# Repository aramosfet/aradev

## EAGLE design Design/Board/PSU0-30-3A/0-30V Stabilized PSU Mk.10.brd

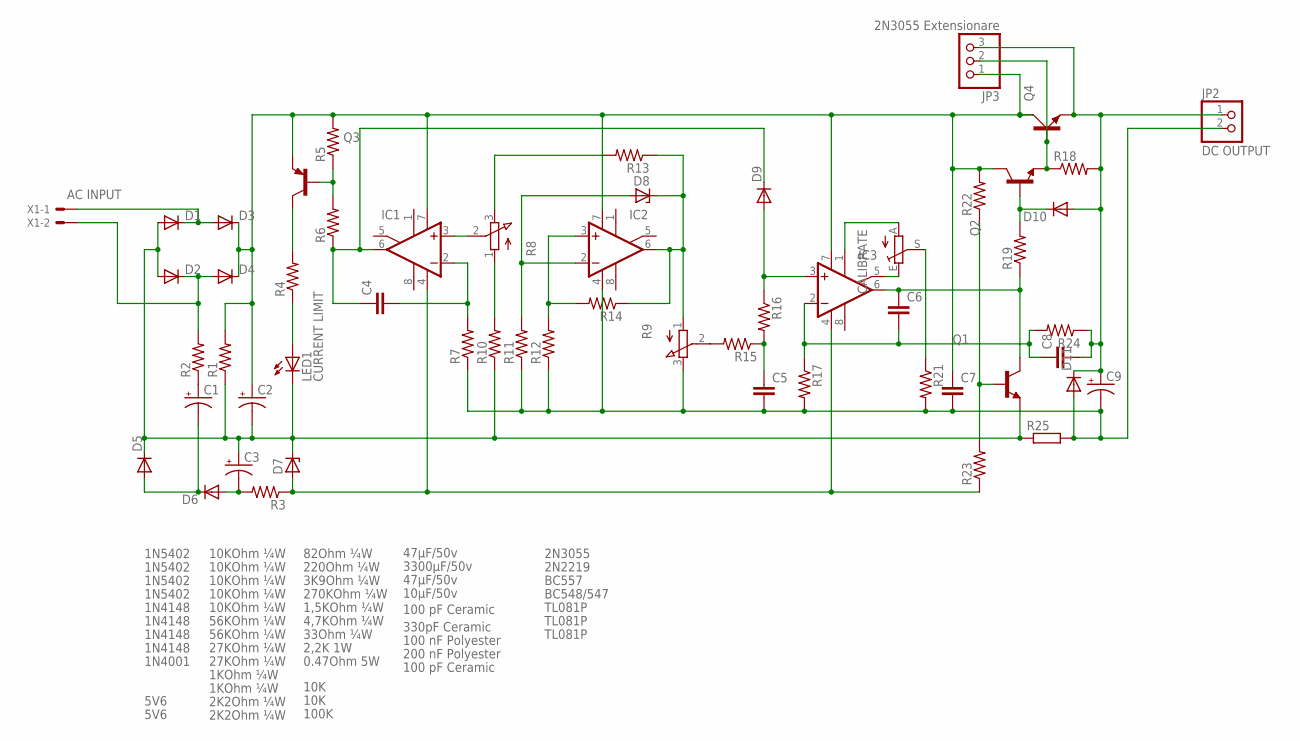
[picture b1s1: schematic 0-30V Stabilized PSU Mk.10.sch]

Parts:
C1, C3: 47µF/50v; TT2D4
C2: 3300µF/50v; EB20D
C4: 330pF Ceramic; C025-024X044
C5: 100 nF Polyester; C050-025X075
C6, C8: 100 pF Ceramic; C050-024X044
C7: 200 nF Polyester; C075-032X103
C9: 10µF/50v; E5-4
CALIBRATE: 100K; CA6V
D1, D2, D3, D4: 1N5402; DO201-15
D5, D6: 1N4148; DO35-10
D7, D8: 5V6; DO34Z7
D9, D10: 1N4148; DO35-7
D11: 1N4001; DO35-7
IC1, IC2, IC3: TL081P; DIL08
JP2: DC OUTPUT; 1X02
JP3: 2N3055 Extensionare; 1X03
LED1: CURRENT LIMIT; LED3MM
Q1: BC548/547; TO92-EBC
Q2: 2N2219; TO5
Q3: BC557; TO92-EBC
Q4: 2N3055; TO3A
R1: 2,2K 1W; P0613/15
R2: 82Ohm ¼W; 0204/7
R3: 220Ohm ¼W; 0204/7
R4: 3K9Ohm ¼W; 0204/7
R5, R16: 2K2Ohm ¼W; 0204/7
R6, R7, R12, R14, R22: 10KOhm ¼W; 0204/7
R8, R9: 10K; 3RP/1610N
R10: 33Ohm ¼W; 0204/7
R11: 4,7KOhm ¼W; 0204/7
R13, R24: 56KOhm ¼W; 0204/7
R15, R17: 27KOhm ¼W; 0204/7
R18, R19: 1KOhm ¼W; 0207/2V
R21: 270KOhm ¼W; 0204/7
R23: 1,5KOhm ¼W; 0204/7
R25: 0.47Ohm 5W; VTA54
X1: AC INPUT; 22-23-2021

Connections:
0-30VDC: C8.2, C9.+, D10.A, D11.C, JP2.1, JP3.3, Q4.E, R18.2, R24.1
0VAC: D1.C, D3.A, X1.1
24VAC: D2.C, D4.A, R2.2, X1.2
GND: C5.2, C7.2, C9.-, D11.A, IC2.4 (V-), JP2.2, R7.1, R9.3 (E), R11.1, R12.1, R17.2, R21.2, R25.2
unnamed: LED1.A, R4.1
unnamed: C1.-, D5.A, D6.C
unnamed: C1.+, R2.1
unnamed: Q3.C, R4.2
unnamed: Q3.B, R5.1, R6.2
unnamed: C3.-, D6.A, R3.2
unnamed: D7.A, IC1.4 (V-), IC3.4 (V-), R3.1, R23.1
unnamed: C4.1, D9.C, IC1.6 (OUT), R6.1
unnamed: C4.2, IC1.2 (-IN), R7.2
unnamed: IC1.3 (+IN), R8.2 (S)
unnamed: R8.1 (A), R10.2
unnamed: C2.-, C3.+, D1.A, D2.A, D5.C, D7.C, LED1.K (C), Q1.E, R1.1, R10.1, R25.1
unnamed: D8.C, IC2.6 (OUT), R9.1 (A), R13.1, R14.1
unnamed: IC2.3 (+IN), R12.2, R14.2
unnamed: D8.A, IC2.2 (-IN), R11.2
unnamed: R8.3 (E), R13.2
unnamed: R9.2 (S), R15.2
unnamed: C5.1, R15.1, R16.2
unnamed: D9.A, IC3.3 (+IN), R16.1
unnamed: JP3.2, Q2.1 (E), Q4.B, R18.1
unnamed: D10.C, Q2.2 (B), R19.2
unnamed: C6.1, IC3.6 (OUT), Q1.C, R19.1
unnamed: CALIBRATE.E, IC3.5 (ON2)
unnamed: CALIBRATE.A, IC3.1 (ON1)
unnamed: CALIBRATE.S, R21.1
unnamed: Q1.B, R22.1, R23.2
unnamed: C2.+, C7.1, D3.C, D4.C, IC1.7 (V+), IC2.7 (V+), IC3.7 (V+), JP3.1, Q2.3 (C), Q3.E, Q4.C, Q4.C1 (C), R1.2, R5.2, R22.2
unnamed: C6.2, C8.1, IC3.2 (-IN), R17.1, R24.2

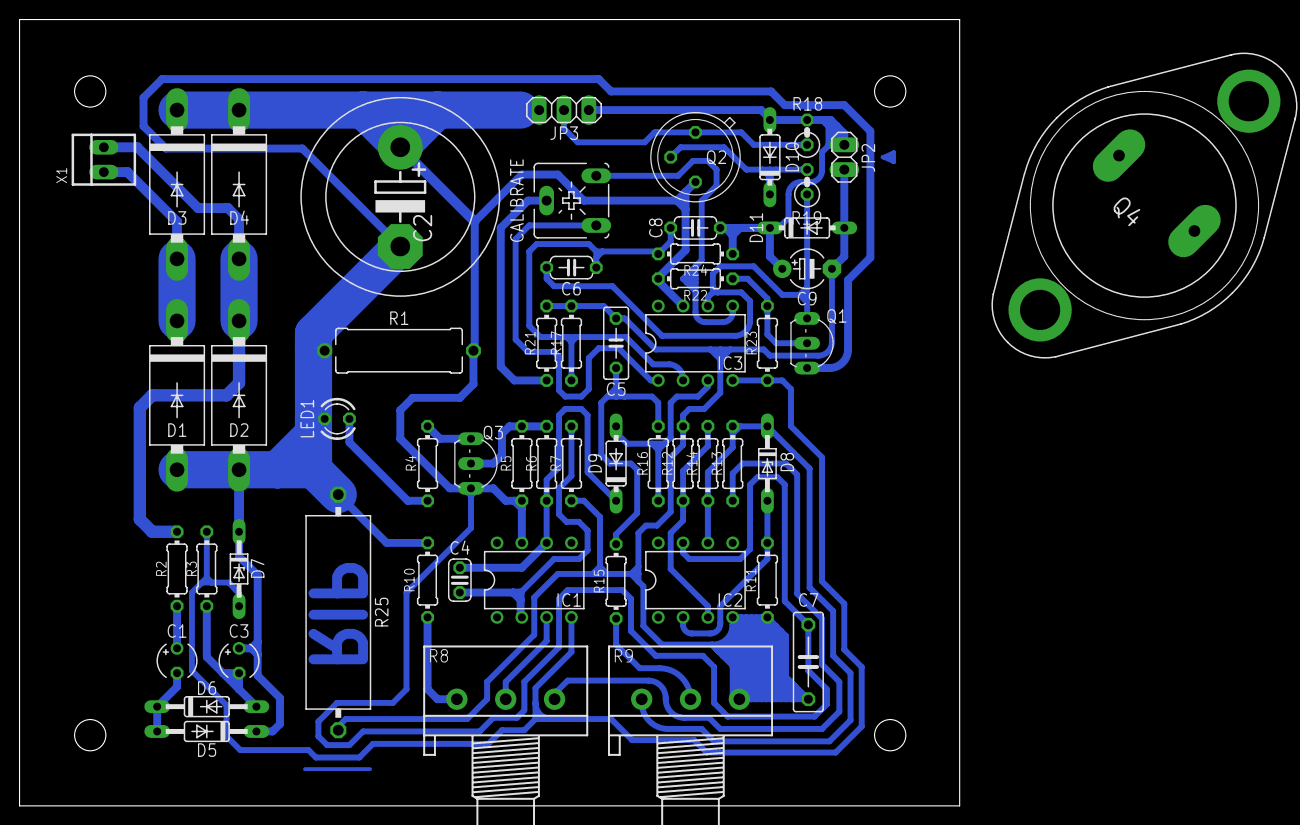
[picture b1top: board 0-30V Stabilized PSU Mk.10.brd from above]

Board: 2 copper layers, 96.3 x 80.5 mm, 56 parts (0 on the bottom side), 32 nets.

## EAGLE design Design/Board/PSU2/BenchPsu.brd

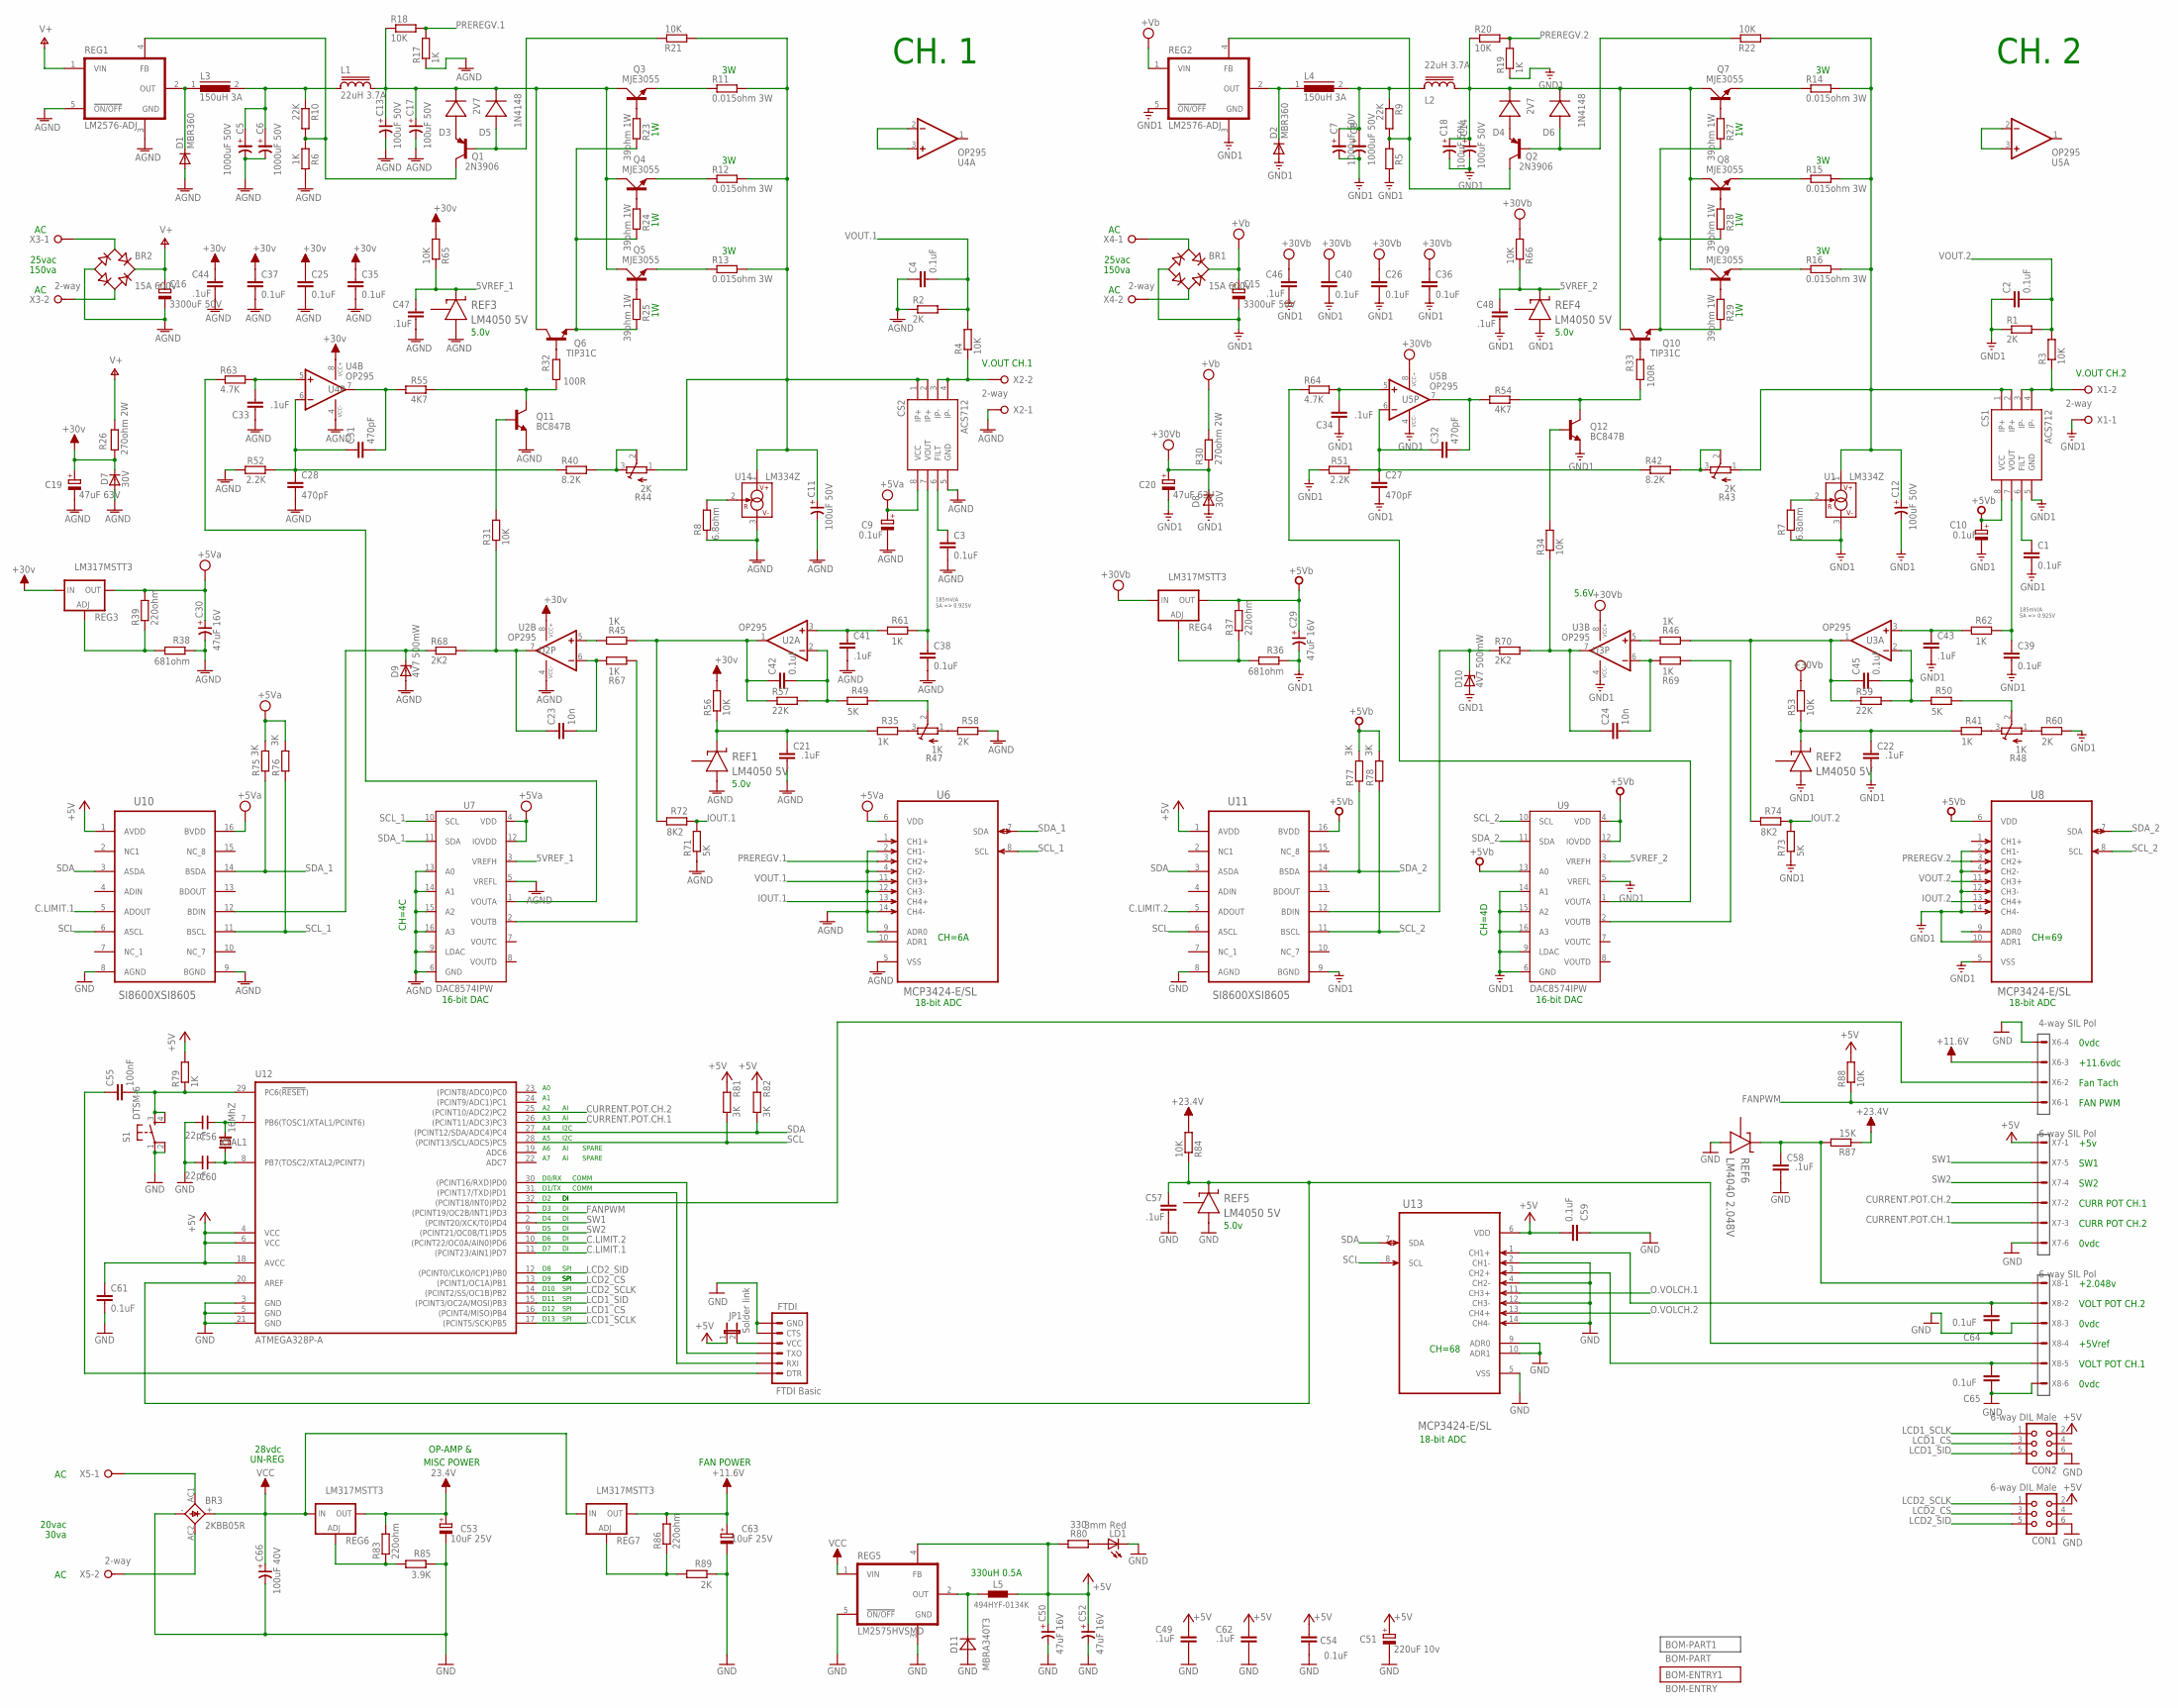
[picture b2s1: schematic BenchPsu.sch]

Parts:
BR1, BR2: 15A 600V; GSIB_15A
BR3: 2KBB05R; 2KBB-R; PARTNO RS 700-5330
C1, C2, C3, C4, C25, C26, C35, C36, C37, C38, C39, C40, C42, C45, C54, C59, C61, C64, C65: 0.1uF; C0805
C5, C6, C7, C8: 1000uF 50V; E5,0-12
C9, C10: 0.1uF; E2-5
C11, C12: 100uF 50V; E-050X125; PARTNO RS 365-4329
C13, C14, C17, C18: 100uF 50V; E-035X080; PARTNO RS 737-4421
C15, C16: 3300uF 50V; E7,5-18; PARTNO RS 684-2030
C19: 47uF 63V; E2,5-7; PARTNO IanJ Stock
C20: 47uF 63V; E2,5-7; PARTNO IanJ stock
C21, C22, C33, C34, C41, C43, C44, C46, C47, C48, C49, C57, C58, C62: .1uF; C0805
C23, C24: 10n; C0805
C27, C28, C31, C32: 470pF; C0805
C29, C50, C52: 47uF 16V; SV-C; PARTNO *
C30: 47uF 16V; SV-C
C51: 220uF 10v; E2-5
C53, C63: 10uF 25V; E2-5
C55: 100nF; C0805
C56, C60: 22pF; ENP-015-040; PARTNO Through hole
C66: 100uF 40V; SV-E/F
CON1, CON2: 6-way DIL Male; CON06
CS1, CS2: ACS712; SO08
D1, D2: MBR360; DO-201-15_V
D3, D4: 2V7; SOD123
D5, D6: 1N4148; SOD123
D7, D8: 30V; D015-12_V
D9, D10: 4V7 500mW; SOD80C
D11: MBRA340T3; SMA
FTDI: FTDI Basic; 1X06
JP1: Solder link; JP1
L1, L2: 22uH 3.7A; RS749-8366_THT22UH; PARTNO RS 749-8366
L3, L4: 150uH 3A; SFT1030; PARTNO RS 742-7991
L5: 494HYF-0134K; 0.2PIN_0.3DIA
LD1: 3mm Red; LED3MM
Q1, Q2: 2N3906; SOT23-BEC
Q3, Q4, Q5, Q7, Q8, Q9: MJE3055; TO220AV
Q6, Q10: TIP31C; TO220V
Q11, Q12: BC847B; SOT23
R1, R2, R58, R60, R89: 2K; R0805
R3, R4, R18, R20, R21, R22, R31, R34, R53, R56, R65, R66, R84, R88: 10K; R0805
R5, R6, R17, R19, R35, R41, R45, R46, R61, R62, R67, R69, R79: 1K; R0805
R7, R8: 6.8ohm; R0805
R9, R10, R57, R59: 22K; R0805
R11, R12, R13, R14, R15, R16: 0.015ohm 3W; R2512; PARTNO RS 720-3164
R23, R24, R25, R27, R28, R29: 39ohm 1W; 0411V
R26, R30: 270ohm 2W; P0613V
R32, R33: 100R; R0805
R36, R38: 681ohm; R0805
R37, R39, R83, R86: 220ohm; R0805
R40, R42: 8.2K; R0805
R43, R44: 2K; SM-42/43W
R47: 1K; 3223W
R48: 1K; SM-42/43W
R49, R50, R71, R73: 5K; R0805
R51, R52: 2.2K; R0805
R54, R55: 4K7; R0805
R63, R64: 4.7K; R0805
R68, R70: 2K2; R0805
R72, R74: 8K2; R0805
R75, R76, R77, R78, R81, R82: 3K; R0805
R80: 330; R0805
R85: 3.9K; R0805
R87: 15K; R0805
REF1, REF2: LM4050 5V; SOT95P237X112-3N
REF3, REF4, REF5: LM4050 5V; SOT95P237X112-3N; MPN LM4040A20IDBZT
REF6: LM4040 2.048V; SOT95P237X112-3N
REG1, REG2: LM2576-ADJ; LM2575HV_V_2
REG3, REG4, REG6, REG7: LM317MSTT3; SOT223
REG5: LM2575HVSMD; TO263-5
S1: DTSM-6
U1, U14: LM334Z; TO92
U2, U3, U4, U5: OP295; SO08
U6, U8, U13: MCP3424-E/SL; SOIC127P600X175-14N
U7, U9: DAC8574IPW; TSSOP16
U10, U11: SI8600XSI8605; SOIC16N
U12: ATMEGA328P-A; TQFP32A
X1, X2, X3, X4, X5: 2-way; W237-132
X6: 4-way SIL Pol; 22-23-2041
X7, X8: 6-way SIL Pol; 22-23-2061
XTAL1: 16MhZ; HC49/S@1

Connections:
2.048V: C58.1, R87.2, REF6.1 (CATHODE), X8.1
5VREF_1: C47.1, R65.1, REF3.1 (CATHODE), U7.3 (VREFH)
5VREF_2: C48.1, R66.1, REF4.1 (CATHODE), U9.3 (VREFH)
+5V: C49.1, C50.+, C51.+, C52.+, C54.2, C59.1, C61.1, C62.1, CON1.2, CON2.2, JP1.1, L5.2, R79.2, R80.1, R81.2, R82.2, R88.2, REG5.4 (FB), U10.1 (AVDD), U11.1 (AVDD), U12.4 (VCC), U12.6 (VCC), U12.18 (AVCC), U13.6 (VDD), X7.1
+5VT: C10.+, C29.+, CS1.8 (VCC), R37.2, R77.2, R78.2, REG4.4 (OUT), U8.6 (VDD), U9.4 (VDD), U9.12 (IOVDD), U9.13 (A0), U11.16 (BVDD)
+12V: C63.+, R86.2, REG7.4 (OUT), X6.3
+24V: C53.+, R83.2, R84.2, R87.1, REG6.4 (OUT)
AGND: BR2.-, C3.2, C4.1, C5.-, C6.-, C9.-, C11.-, C13.-, C16.-, C17.-, C19.-, C21.2, C25.2, C28.2, C30.-, C33.1, C35.2, C37.2, C38.2, C41.2, C44.2, C47.2, CS2.5 (GND), D1.A, D7.A, D9.A, Q11.2 (E), R2.1, R6.2, R8.1, R17.1, R38.1, R52.1, R58.2, R71.1, REF1.2 (A), REF3.2 (A), REG1.3 (GND), REG1.5 (!ON/OFF), U2.4 (VCC-), U4.4 (VCC-), U6.2 (CH1-), U6.4 (CH2-), U6.5 (VSS), U6.9 (ADR0), U6.12 (CH3-), U6.14 (CH4-), U7.5 (VREFL), U7.6 (GND), U7.9 (LDAC), U7.13 (A0), U7.14 (A1), U7.15 (A2), U7.16 (A3), U10.9 (BGND), U14.3 (V-), X2.1
AVCC: C19.+, C25.1, C35.1, C37.1, C44.1, D7.C, R26.1, R56.2, R65.2, REG3.3 (IN), U2.8 (VCC+), U4.8 (VCC+)
C.LIMIT.1: U10.5 (ADOUT), U12.11 ((PCINT23/AIN1)PD7)
C.LIMIT.2: U11.5 (ADOUT), U12.10 ((PCINT22/OC0A/AIN0)PD6)
CURRENT.POT.CH.1: U12.26 ((PCINT11/ADC3)PC3), X7.3
CURRENT.POT.CH.2: U12.25 ((PCINT10/ADC2)PC2), X7.2
FANPWM: R88.1, U12.1 ((PCINT19/OC2B/INT1)PD3), X6.1
GND: BR3.-, C49.2, C50.-, C51.-, C52.-, C53.-, C54.1, C56.1, C57.2, C58.2, C59.2, C60.1, C61.2, C62.2, C63.-, C64.2, C65.2, C66.-, CON1.6, CON2.6, D11.A, FTDI.5 (CTS), FTDI.6 (GND), LD1.K (C), R85.1, R89.1, REF5.2 (A), REF6.2 (A), REG5.3 (GND), REG5.5 (!ON/OFF), S1.1, S1.2, U10.8 (AGND), U11.8 (AGND), U12.3 (GND), U12.5 (GND), U12.21 (GND), U13.2 (CH1-), U13.4 (CH2-), U13.5 (VSS), U13.9 (ADR0), U13.10 (ADR1), U13.12 (CH3-), U13.14 (CH4-), X6.4, X7.6, X8.3, X8.6
GND1: BR1.-, C1.2, C2.1, C7.-, C8.-, C10.-, C12.-, C14.-, C15.-, C18.-, C20.-, C22.2, C26.2, C27.2, C29.-, C34.1, C36.2, C39.2, C40.2, C43.2, C46.2, C48.2, CS1.5 (GND), D2.A, D8.A, D10.A, Q12.2 (E), R1.1, R5.2, R7.1, R19.1, R36.1, R51.1, R60.2, R73.1, REF2.2 (A), REF4.2 (A), REG2.3 (GND), REG2.5 (!ON/OFF), U1.3 (V-), U3.4 (VCC-), U5.4 (VCC-), U8.2 (CH1-), U8.4 (CH2-), U8.5 (VSS), U8.10 (ADR1), U8.12 (CH3-), U8.14 (CH4-), U9.5 (VREFL), U9.6 (GND), U9.9 (LDAC), U9.14 (A1), U9.15 (A2), U9.16 (A3), U11.9 (BGND), X1.1
IOUT.1: R71.2, R72.2, U6.13 (CH4+)
IOUT.2: R73.2, R74.2, U8.13 (CH4+)
LCD1_CS: CON2.3, U12.16 ((PCINT4/MISO)PB4)
LCD1_SCLK: CON2.1, U12.17 ((PCINT5/SCK)PB5)
LCD1_SID: CON2.5, U12.15 ((PCINT3/OC2A/MOSI)PB3)
LCD2_CS: CON1.3, U12.13 ((PCINT1/OC1A)PB1)
LCD2_SCLK: CON1.1, U12.14 ((PCINT2/SS/OC1B)PB2)
LCD2_SID: CON1.5, U12.12 ((PCINT0/CLKO/ICP1)PB0)
unnamed: R38.2, R39.1, REG3.1 (ADJ)
unnamed: BR3.AC1, X5.1
unnamed: D11.C, L5.1, REG5.2 (OUT)
unnamed: BR3.AC2, X5.2
unnamed: R47.2 (S), R49.2
unnamed: C42.2, R49.1, R57.2, U2.2 (-IN)
unnamed: C5.+, C6.+, L1.1, L3.2, R10.1
unnamed: C41.1, R61.1, U2.3 (+IN)
unnamed: Q1.C, R6.1, R10.2, REG1.4 (FB)
unnamed: D3.A (+), Q1.E
unnamed: D5.A (+), Q1.B, R21.2
unnamed: R83.1, R85.2, REG6.1 (ADJ)
unnamed: C31.2, R55.1, U4.7 (OUT)
unnamed: C28.1, C31.1, R40.1, R52.2, U4.6 (-IN)
unnamed: Q11.1 (B), R31.2
unnamed: C23.1, R31.1, R68.2, U2.7 (OUT)
unnamed: R40.2, R44.2 (S), R44.3 (E)
unnamed: R64.1, U9.1 (VOUTA)
unnamed: BR2.AC1, X3.1
unnamed: U12.32 ((PCINT18/INT0)PD2), X6.2
unnamed: LD1.A, R80.2
unnamed: C57.1, R84.1, REF5.1 (CATHODE), U12.20 (AREF), X8.4
unnamed: C38.1, CS2.7 (VOUT), R61.2
unnamed: Q3.B, R23.1
unnamed: C55.1, FTDI.1 (DTR)
unnamed: C33.2, R63.2, U4.5 (+IN)
unnamed: R35.2, R47.3 (E)
unnamed: Q4.B, R24.1
unnamed: R69.2, U9.2 (VOUTB)
unnamed: U4.2 (-IN), U4.3 (+IN)
unnamed: D10.C, R70.1, U11.12 (BDIN)
unnamed: R47.1 (A), R58.1
unnamed: FTDI.4 (VCC), JP1.2
unnamed: R63.1, U7.1 (VOUTA)
unnamed: Q11.3 (C), R32.2, R55.2
unnamed: C56.2, U12.7 (PB6(TOSC1/XTAL1/PCINT6)), XTAL1.2
unnamed: C60.2, U12.8 (PB7(TOSC2/XTAL2/PCINT7)), XTAL1.1
unnamed: U5.2 (-IN), U5.3 (+IN)
unnamed: C55.2, R79.1, S1.3, S1.4, U12.29 (PC6(!RESET!))
unnamed: R36.2, R37.1, REG4.1 (ADJ)
unnamed: R41.2, R48.3 (E)
unnamed: R48.1 (A), R60.1
unnamed: R8.2, U14.2 (R)
unnamed: C22.1, R41.1, R53.1, REF2.1 (CATHODE)
unnamed: D9.C, R68.1, U10.12 (BDIN)
unnamed: Q5.B, R25.1
unnamed: C3.1, CS2.6 (FILT)
unnamed: C65.1, U13.3 (CH2+), X8.5
unnamed: C45.2, R50.1, R59.2, U3.2 (-IN)
unnamed: C43.1, R62.1, U3.3 (+IN)
unnamed: R86.1, R89.2, REG7.1 (ADJ)
unnamed: FTDI.2 (RXI), U12.31 ((PCINT17/TXD)PD1)
unnamed: R45.1, U2.5 (+IN)
unnamed: FTDI.3 (TXO), U12.30 ((PCINT16/RXD)PD0)
unnamed: C23.2, R67.1, U2.6 (-IN)
unnamed: D2.C, L4.1, REG2.2 (OUT)
unnamed: C27.1, C32.1, R42.1, R51.2, U5.6 (-IN)
unnamed: Q12.1 (B), R34.2
unnamed: C24.1, R34.1, R70.2, U3.7 (OUT)
unnamed: C39.1, CS1.7 (VOUT), R62.2
unnamed: R7.2, U1.2 (R)
unnamed: C7.+, C8.+, L2.1, L4.2, R9.1
unnamed: C34.2, R64.2, U5.5 (+IN)
unnamed: CS1.3 (IP-), CS1.4 (IP-), R3.1, X1.2
unnamed: C1.1, CS1.6 (FILT)
unnamed: C32.2, R54.1, U5.7 (OUT)
unnamed: D4.A (+), Q2.E
unnamed: Q12.3 (C), R33.2, R54.2
unnamed: D6.A (+), Q2.B, R22.2
unnamed: R48.2 (S), R50.2
unnamed: C24.2, R69.1, U3.6 (-IN)
unnamed: R46.1, U3.5 (+IN)
unnamed: R42.2, R43.2 (S), R43.3 (E)
unnamed: Q10.3 (E), R27.2, R28.2, R29.2
unnamed: C64.1, U13.1 (CH1+), X8.2
unnamed: BR1.AC2, X4.2
unnamed: Q6.3 (E), R23.2, R24.2, R25.2
unnamed: Q8.E, R15.1
unnamed: C21.1, R35.1, R56.1, REF1.1 (CATHODE)
unnamed: BR1.AC1, X4.1
unnamed: R67.2, U7.2 (VOUTB)
unnamed: CS2.3 (IP-), CS2.4 (IP-), R4.1, X2.2
unnamed: Q9.B, R29.1
unnamed: C11.+, CS2.1 (IP+), CS2.2 (IP+), R11.2, R12.2, R13.2, R21.1, R44.1 (A), U14.1 (V+)
unnamed: Q5.E, R13.1
unnamed: Q6.1 (B), R32.1
unnamed: Q9.E, R16.1
unnamed: Q7.B, R27.1
unnamed: Q8.B, R28.1
unnamed: Q10.1 (B), R33.1
unnamed: D1.C, L3.1, REG1.2 (OUT)
unnamed: Q3.E, R11.1
unnamed: Q4.E, R12.1
unnamed: BR2.AC2, X3.2
unnamed: Q7.E, R14.1
unnamed: C14.+, C18.+, D4.C (-), D6.C (-), L2.2, Q7.C, Q8.C, Q9.C, Q10.2 (C), R20.1
unnamed: Q2.C, R5.1, R9.2, REG2.4 (FB)
unnamed: C12.+, CS1.1 (IP+), CS1.2 (IP+), R14.2, R15.2, R16.2, R22.1, R43.1 (A), U1.1 (V+)
O.VOLCH.1: U13.11 (CH3+)
O.VOLCH.2: U13.13 (CH4+)
PREREGV.1: R17.2, R18.2, U6.3 (CH2+)
PREREGV.2: R19.2, R20.2, U8.3 (CH2+)
PREVOUT.1: C13.+, C17.+, D3.C (-), D5.C (-), L1.2, Q3.C, Q4.C, Q5.C, Q6.2 (C), R18.1
QQQ: C42.1, R45.2, R57.1, R72.1, U2.1 (OUT)
QQQ1: C45.1, R46.2, R59.1, R74.1, U3.1 (OUT)
SCL: R81.1, U10.6 (ASCL), U11.6 (ASCL), U12.28 ((PCINT13/SCL/ADC5)PC5), U13.8 (SCL)
SCL_1: R76.1, U6.8 (SCL), U7.10 (SCL), U10.11 (BSCL)
SCL_2: R78.1, U8.8 (SCL), U9.10 (SCL), U11.11 (BSCL)
SDA: R82.1, U10.3 (ASDA), U11.3 (ASDA), U12.27 ((PCINT12/SDA/ADC4)PC4), U13.7 (SDA)
SDA_1: R75.1, U6.7 (SDA), U7.11 (SDA), U10.14 (BSDA)
SDA_2: R77.1, U8.7 (SDA), U9.11 (SDA), U11.14 (BSDA)
SW1: U12.2 ((PCINT20/XCK/T0)PD4), X7.5
SW2: U12.9 ((PCINT21/OC0B/T1)PD5), X7.4
V+: BR2.+, C16.+, R26.2, REG1.1 (VIN)
VCC: BR3.+, C66.+, REG5.1 (VIN), REG6.3 (IN), REG7.3 (IN)
VDD: C20.+, C26.1, C36.1, C40.1, C46.1, D8.C, R30.1, R53.2, R66.2, REG4.3 (IN), U3.8 (VCC+), U5.8 (VCC+)
VEE: BR1.+, C15.+, R30.2, REG2.1 (VIN)
VOUT.1: C4.2, R2.2, R4.2, U6.11 (CH3+)
VOUT.2: C2.2, R1.2, R3.2, U8.11 (CH3+)
VPP: C9.+, C30.+, CS2.8 (VCC), R39.2, R75.2, R76.2, REG3.4 (OUT), U6.6 (VDD), U7.4 (VDD), U7.12 (IOVDD), U10.16 (BVDD)

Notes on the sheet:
330uH 0.5A
V.OUT CH.1
185mV/A 5A => 0.925V
D0/RX
D1/TX
D10
D11
D12
D13
I2C
SPI
COMM
SW2
SW1
0vdc
VOLT POT CH.2
VOLT POT CH.1
+2.048v
+5v
V.OUT CH.2
5.6V
20vac
UN-REG
25vac
150va
30va
CURR POT CH.2
CURR POT CH.1
28vdc
CH. 1
+11.6vdc
Fan Tach
FAN PWM
FAN POWER
16-bit DAC
18-bit ADC
5.0v
+5Vref
MISC POWER
OP-AMP &

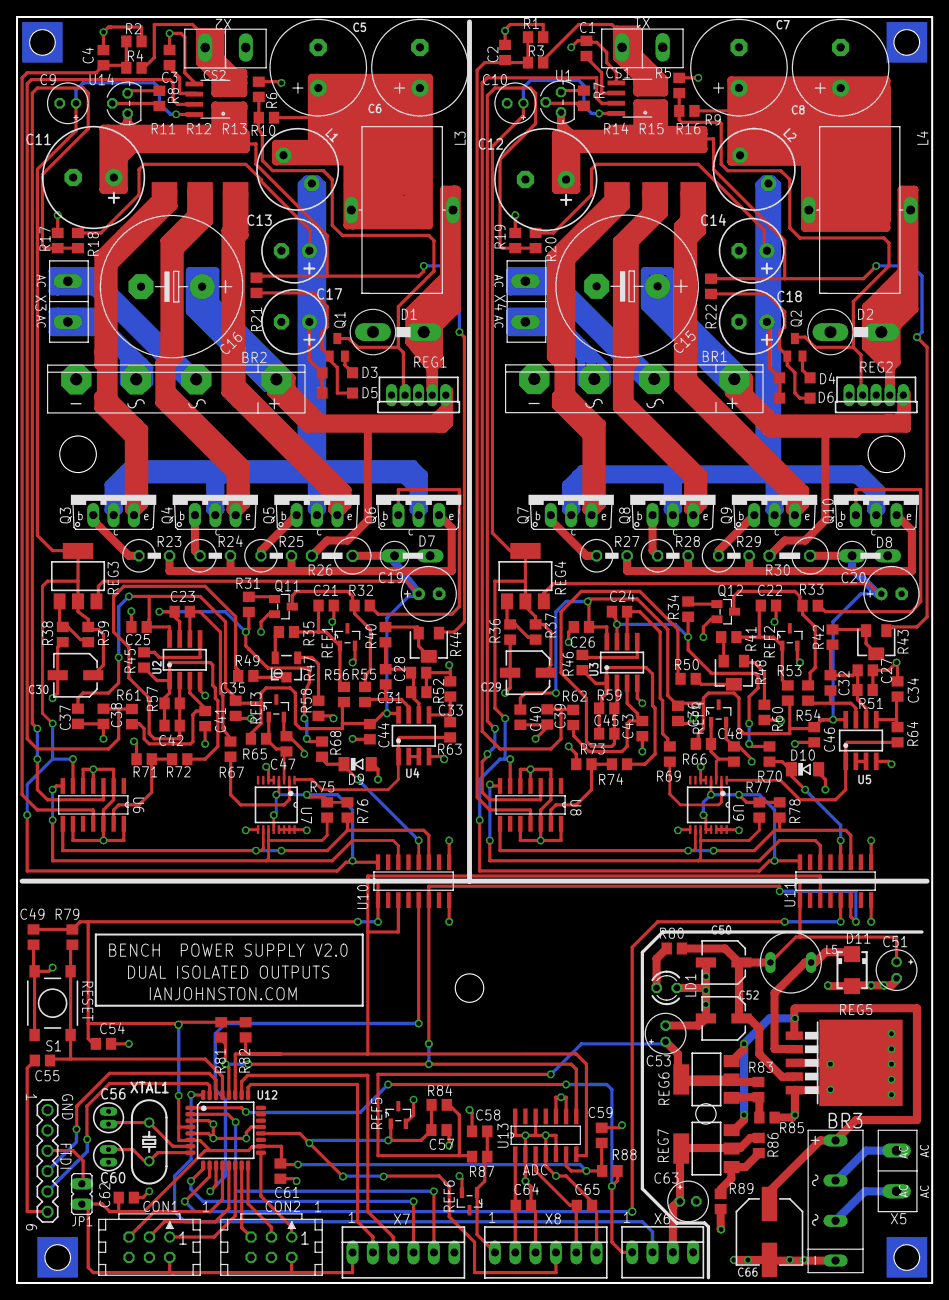
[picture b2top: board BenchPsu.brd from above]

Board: 2 copper layers, 114.3 x 158.1 mm, 230 parts (0 on the bottom side), 142 nets.

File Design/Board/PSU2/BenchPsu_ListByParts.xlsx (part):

Part | Value | Attributes | Package | Description | Part Num
BOM-ENTRY1 | BOM-ENTRY |  | * | BOM ENTRY | *
BOM-PART1 | BOM-PART |  | * | BOM ENTRY | *
BR1 | 15A 600V |  | GSIB_15A |  | *
BR2 | 15A 600V |  | GSIB_15A |  | *
BR3 | 2KBB05R |  | 2KBB-R | RECTIFIER | RS 700-5330
C1 | 0.1uF |  | C0805 | CAPACITOR, European symbol | *
C2 | 0.1uF |  | C0805 | CAPACITOR, European symbol | *
C3 | 0.1uF |  | C0805 | CAPACITOR, European symbol | *
C4 | 0.1uF |  | C0805 | CAPACITOR, European symbol | *
C5 | 1000uF 50V |  | E5,0-12 | POLARIZED RADIAL ELECTROLYTIC | *
C6 | 1000uF 50V |  | E5,0-12 | POLARIZED RADIAL ELECTROLYTIC | *
C7 | 1000uF 50V |  | E5,0-12 | POLARIZED RADIAL ELECTROLYTIC | *
C8 | 1000uF 50V |  | E5,0-12 | POLARIZED RADIAL ELECTROLYTIC | *
C9 | 0.1uF |  | E2-5 | POLARIZED CAPACITOR, European symbol | *
C10 | 0.1uF |  | E2-5 | POLARIZED CAPACITOR, European symbol | *
C11 | 100uF 50V |  | E-050X125 | POLARIZED CAP
C12 | 100uF 50V |  | E-050X125 | POLARIZED CAP
C13 | 100uF 50V |  | E-035X080 | POLARIZED CAP | RS 737-4421
C14 | 100uF 50V |  | E-035X080 | POLARIZED CAP | RS 737-4421
C15 | 3300uF 50V |  | E7,5-18 | POLARIZED CAPACITOR, European symbol | RS 684-2030
C16 | 3300uF 50V |  | E7,5-18 | POLARIZED CAPACITOR, European symbol | RS 684-2030
C17 | 100uF 50V |  | E-035X080 | POLARIZED CAP | RS 737-4421
C18 | 100uF 50V |  | E-035X080 | POLARIZED CAP | RS 737-4421
C19 | 47uF 63V |  | E2,5-7 | POLARIZED CAPACITOR, European symbol | IANJ STOCK
C20 | 47uF 63V |  | E2,5-7 | POLARIZED CAPACITOR, European symbol | IANJ STOCK
C21 | .1uF |  | C0805 | CAPACITOR, European symbol | *
C22 | .1uF |  | C0805 | CAPACITOR, European symbol | *
C23 | 10n |  | C0805 | CAPACITOR, European symbol | *
C24 | 10n |  | C0805 | CAPACITOR, European symbol | *
C25 | 0.1uF |  | C0805 | CAPACITOR, European symbol | *
C26 | 0.1uF |  | C0805 | CAPACITOR, European symbol | *
C27 | 470pF |  | C0805 | CAPACITOR, European symbol | *
C28 | 470pF |  | C0805 | CAPACITOR, European symbol | *
C29 | 47uF 16V |  | SV-C | POLARIZED CAP | *
C30 | 47uF 16V |  | SV-C | POLARIZED CAP | *
C31 | 470pF |  | C0805 | CAPACITOR, European symbol | *
C32 | 470pF |  | C0805 | CAPACITOR, European symbol | *
C33 | .1uF |  | C0805 | CAPACITOR, European symbol | *
C34 | .1uF |  | C0805 | CAPACITOR, European symbol | *
C35 | 0.1uF |  | C0805 | CAPACITOR, European symbol | *
C36 | 0.1uF |  | C0805 | CAPACITOR, European symbol | *
C37 | 0.1uF |  | C0805 | CAPACITOR, European symbol | *
C38 | 0.1uF |  | C0805 | CAPACITOR, European symbol | *
C39 | 0.1uF |  | C0805 | CAPACITOR, European symbol | *
C40 | 0.1uF |  | C0805 | CAPACITOR, European symbol | *
C41 | .1uF |  | C0805 | CAPACITOR, European symbol | *
C42 | 0.1uF |  | C0805 | CAPACITOR, European symbol | *
C43 | .1uF |  | C0805 | CAPACITOR, European symbol | *
C44 | .1uF |  | C0805 | CAPACITOR, European symbol | *
C45 | 0.1uF |  | C0805 | CAPACITOR, European symbol | *
C46 | .1uF |  | C0805 | CAPACITOR, European symbol | *
C47 | .1uF |  | C0805 | CAPACITOR, European symbol | *
C48 | .1uF |  | C0805 | CAPACITOR, European symbol | *
C49 | .1uF |  | C0805 | CAPACITOR, European symbol | *
C50 | 47uF 16V |  | SV-C | POLARIZED CAP | *
C51 | 220uF 10v |  | E2-5 | POLARIZED CAPACITOR, European symbol | *
C52 | 47uF 16V |  | SV-C | POLARIZED CAP | *
C53 | 10uF 25V |  | E2-5 | POLARIZED CAPACITOR, European symbol | *
C54 | 0.1uF |  | C0805 | CAPACITOR, European symbol | *
C55 | 100nF |  | C0805 | CAPACITOR, European symbol | *
C56 | 22pF |  | ENP-015-040 | BIPOLAR CAP | THROUGH HOLE
C57 | .1uF |  | C0805 | CAPACITOR, European symbol | *
C58 | .1uF |  | C0805 | CAPACITOR, European symbol | *
C59 | 0.1uF |  | C0805 | CAPACITOR, European symbol | *
C60 | 22pF |  | ENP-015-040 | BIPOLAR CAP | THROUGH HOLE
C61 | 0.1uF |  | C0805 | CAPACITOR, European symbol | *
C62 | .1uF |  | C0805 | CAPACITOR, European symbol | *
C63 | 10uF 25V |  | E2-5 | POLARIZED CAPACITOR, European symbol | *
C64 | 0.1uF |  | C0805 | CAPACITOR, European symbol | *
C65 | 0.1uF |  | C0805 | CAPACITOR, European symbol | *
C66 | 100uF 40V |  | SV-E/F | POLARIZED CAP | *
CON1 | 6-way DIL Male |  | CON06 | CONNECTOR | *
CON2 | 6-way DIL Male |  | CON06 | CONNECTOR | *
CS1 | ACS712 |  | SO08 |  | *
CS2 | ACS712 |  | SO08 |  | *
D1 | MBR360 |  | DO-201-15_V | DIODE | *
D2 | MBR360 |  | DO-201-15_V | DIODE | *
D3 | 2V7 |  | SOD123 |  | *
D4 | 2V7 |  | SOD123 |  | *
D5 | 1N4148 |  | SOD123 |  | *
D6 | 1N4148 |  | SOD123 |  | *
D7 | 30V |  | D015-12_V | DIODE | *
D8 | 30V |  | D015-12_V | DIODE | *
D9 | 4V7 500mW |  | SOD80C | Z-Diode | *
D10 | 4V7 500mW |  | SOD80C | Z-Diode | *
D11 | MBRA340T3 |  | SMA | Surface Mount Schottky Power Rectifier | *
FTDI | FTDI Basic |  | 1X06 |  | *
JP1 | Solder link |  | JP1 | JUMPER | *
L1 | 22uH 3.7A |  | RS749-8366_THT22UH | INDUCTOR | RS 749-8366
L2 | 22uH 3.7A |  | RS749-8366_THT22UH | INDUCTOR | RS 749-8366
L3 | 150uH 3A |  | SFT1030 | INDUCTOR | RS 742-7991
L4 | 150uH 3A |  | SFT1030 | INDUCTOR | RS 742-7991
L5 | 494HYF-0134K |  | 0.2PIN_0.3DIA | 330uH 0.54A | *
LD1 | 3mm Red |  | LED3MM | LED | *
Q1 | 2N3906 |  | SOT23-BEC | PNP Transistror | *
Q2 | 2N3906 |  | SOT23-BEC | PNP Transistror | *
Q3 | MJE3055 |  | TO220AV | NPN TRANSISTOR | *
Q4 | MJE3055 |  | TO220AV | NPN TRANSISTOR | *
Q5 | MJE3055 |  | TO220AV | NPN TRANSISTOR | *
Q6 | TIP31C |  | TO220V | NPN Transistor | *
Q7 | MJE3055 |  | TO220AV | NPN TRANSISTOR | *
Q8 | MJE3055 |  | TO220AV | NPN TRANSISTOR | *
Q9 | MJE3055 |  | TO220AV | NPN TRANSISTOR | *
Q10 | TIP31C |  | TO220V | NPN Transistor | *
Q11 | BC847B |  | SOT23 | NPN Transistor | *
Q12 | BC847B |  | SOT23 | NPN Transistor | *
R1 | 2K |  | R0805 | RESISTOR, European symbol | *
R2 | 2K |  | R0805 | RESISTOR, European symbol | *
R3 | 10K |  | R0805 | RESISTOR, European symbol | *
R4 | 10K |  | R0805 | RESISTOR, European symbol | *
R5 | 1K |  | R0805 | RESISTOR, European symbol | *
R6 | 1K |  | R0805 | RESISTOR, European symbol | *
R7 | 6.8ohm |  | R0805 | RESISTOR, European symbol | *
R8 | 6.8ohm |  | R0805 | RESISTOR, European symbol | *
R9 | 22K |  | R0805 | RESISTOR, European symbol | *
R10 | 22K |  | R0805 | RESISTOR, European symbol | *
R11 | 0.015ohm 3W |  | R2512 | RESISTOR, European symbol | RS 720-3164
R12 | 0.015ohm 3W |  | R2512 | RESISTOR, European symbol | RS 720-3164
R13 | 0.015ohm 3W |  | R2512 | RESISTOR, European symbol | RS 720-3164
R14 | 0.015ohm 3W |  | R2512 | RESISTOR, European symbol | RS 720-3164
R15 | 0.015ohm 3W |  | R2512 | RESISTOR, European symbol | RS 720-3164
R16 | 0.015ohm 3W |  | R2512 | RESISTOR, European symbol | RS 720-3164
R17 | 1K |  | R0805 | RESISTOR, European symbol | *
R18 | 10K |  | R0805 | RESISTOR, European symbol | *
R19 | 1K |  | R0805 | RESISTOR, European symbol | *
R20 | 10K |  | R0805 | RESISTOR, European symbol | *
R21 | 10K |  | R0805 | RESISTOR, European symbol | *
R22 | 10K |  | R0805 | RESISTOR, European symbol | *
R23 | 39ohm 1W |  | 0411V | RESISTOR, European symbol | *
R24 | 39ohm 1W |  | 0411V | RESISTOR, European symbol | *
R25 | 39ohm 1W |  | 0411V | RESISTOR, European symbol | *
R26 | 270ohm 2W |  | P0613V | RESISTOR, European symbol | *
R27 | 39ohm 1W |  | 0411V | RESISTOR, European symbol | *
R28 | 39ohm 1W |  | 0411V | RESISTOR, European symbol | *
R29 | 39ohm 1W |  | 0411V | RESISTOR, European symbol | *
R30 | 270ohm 2W |  | P0613V | RESISTOR, European symbol | *
R31 | 10K |  | R0805 | RESISTOR, European symbol | *
R32 | 100R |  | R0805 | RESISTOR, European symbol | *
R33 | 100R |  | R0805 | RESISTOR, European symbol | *
R34 | 10K |  | R0805 | RESISTOR, European symbol | *
R35 | 1K |  | R0805 | RESISTOR, European symbol | *
R36 | 681ohm |  | R0805 | RESISTOR, European symbol | *
R37 | 220ohm |  | R0805 | RESISTOR, European symbol | *
R38 | 681ohm |  | R0805 | RESISTOR, European symbol | *
R39 | 220ohm |  | R0805 | RESISTOR, European symbol | *
R40 | 8.2K |  | R0805 | RESISTOR, European symbol | *
R41 | 1K |  | R0805 | RESISTOR, European symbol | *
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
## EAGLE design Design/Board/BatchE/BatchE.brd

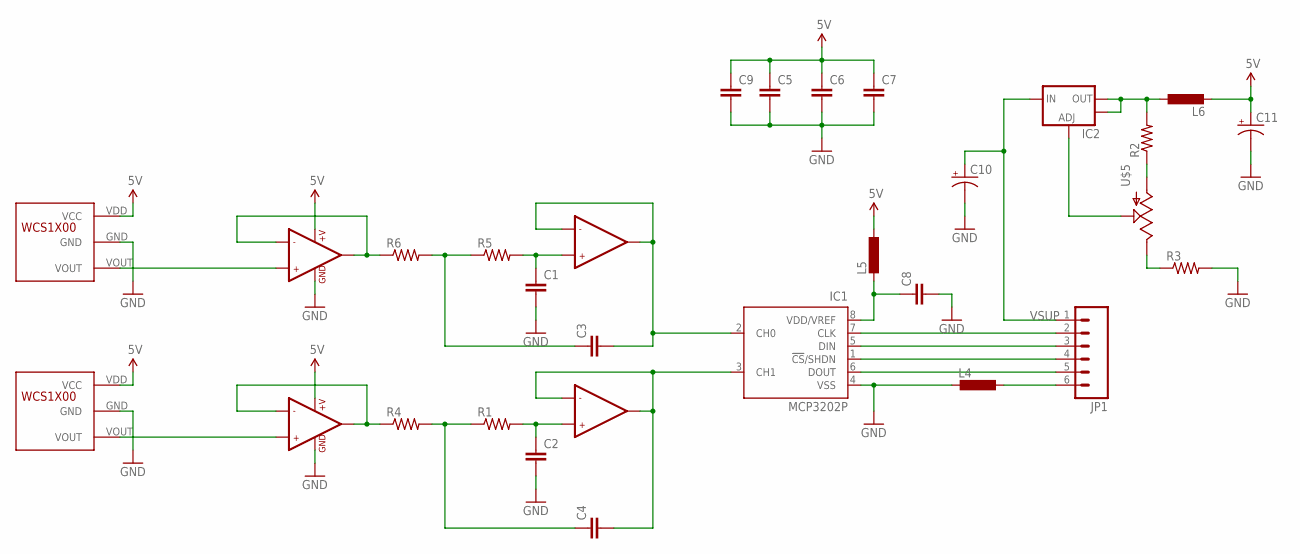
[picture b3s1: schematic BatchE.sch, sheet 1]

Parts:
C1, C2, C3, C4, C5, C6, C7, C8, C9: CAP1206; 1206
C10: CAP_POLPTH4; CPOL-RADIAL-1000UF-25V
C11: CAP_POLPTH1; CPOL-RADIAL-100UF-25V
IC1: MCP3202P; DIL8
IC2: V_REG_LM1117SOT223; SOT223
JP1: M06LONGPADS; 1X06_LONGPADS
L4, L5, L6: L-EU0204V; 0204V
R1, R2, R3, R4, R5, R6: RESISTOR1206; 1206
U$1, U$2: LMV358; SO08
U$3, U$4: WCS1X00
U$5: POTTRIM; TRIM_POT

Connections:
5V: C5.1, C6.1, C7.1, C9.1, C11.1 (+), L5.1, L6.2, U$1.8 (+V), U$2.8 (+V), U$3.VDD (VCC), U$4.VDD (VCC)
GND: C1.2, C2.2, C5.2, C6.2, C7.2, C8.2, C9.2, C10.2 (-), C11.2 (-), IC1.4 (VSS), L4.2, R3.2, U$1.4 (GND), U$2.4 (GND), U$3.GND, U$4.GND; also elsewhere on the board
unnamed: R6.1, U$1.1 (OUT1), U$1.2 (-IN1)
unnamed: R4.1, U$2.1 (OUT1), U$2.2 (-IN1)
unnamed: C3.1, R5.1, R6.2
unnamed: C1.1, R5.2, U$1.5 (+IN2)
unnamed: C3.2, IC1.2 (CH0), U$1.6 (-IN2), U$1.7 (OUT2)
unnamed: U$1.3 (+IN1), U$3.VOUT
unnamed: C4.2, IC1.3 (CH1), U$2.6 (-IN2), U$2.7 (OUT2)
unnamed: C2.1, R1.2, U$2.5 (+IN2)
unnamed: C4.1, R1.1, R4.2
unnamed: U$2.3 (+IN1), U$4.VOUT
unnamed: R2.1, U$5.3 (A)
unnamed: IC2.1 (ADJ), U$5.1 (S)
unnamed: IC1.7 (CLK), JP1.2
unnamed: IC1.5 (DIN), JP1.3
unnamed: IC1.1 (!CS!/SHDN), JP1.4
unnamed: IC1.6 (DOUT), JP1.5
unnamed: IC2.2 (OUT), IC2.4 (OUT), L6.1, R2.2
unnamed: R3.1, U$5.2 (E)
unnamed: JP1.6, L4.1
unnamed: C8.1, IC1.8 (VDD/VREF), L5.2
VSUP: C10.1 (+), IC2.3 (IN), JP1.1

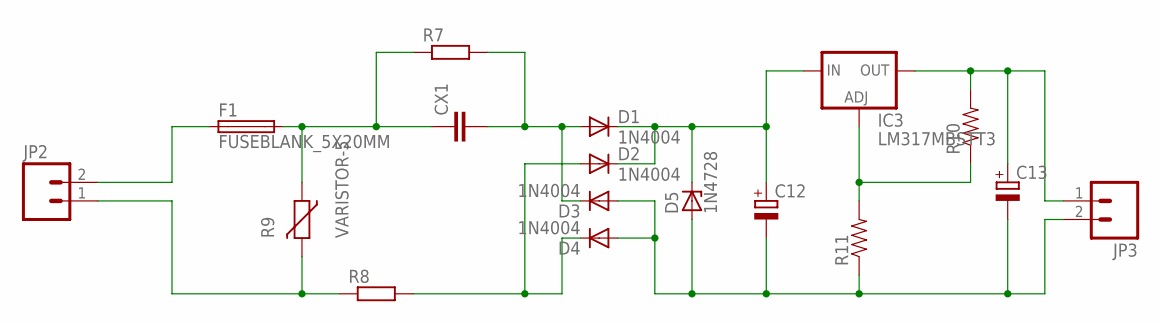
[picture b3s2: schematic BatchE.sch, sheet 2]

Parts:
C12, C13: CPOL-EUE5-8.5; E5-8,5
CX1: CXXC15B8; XC15B8
D1, D2, D3, D4: 1N4004; DO41-10
D5: 1N4728; DO41Z10
F1: FUSEBLANK_5X20MM; FUSE_HOLDER_5X20MM
IC3: LM317MBSTT3; SOT223
JP2, JP3: M023.5MM; SCREWTERMINAL-3.5MM-2
R7, R8: R-EU_0207/12; 0207/12
R9: VARISTOR-5; R-5
R10, R11: RESISTOR0805-RES; 0805

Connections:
unnamed: F1.1, JP2.2
unnamed: CX1.1, F1.2, R7.1, R9.1
unnamed: CX1.2, D1.A, D3.C, R7.2
unnamed: D2.A, D4.C, R8.2
unnamed: JP2.1, R8.1, R9.2
unnamed: C12.+, D1.C, D2.C, D5.C, IC3.3 (IN)
unnamed: IC3.1 (ADJ), R10.1, R11.2
unnamed: C12.-, C13.-, D3.A, D4.A, D5.A, JP3.2, R11.1
unnamed: C13.+, IC3.4 (OUT), JP3.1, R10.2

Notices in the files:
parts and their libraries:
SparkFun-Displays: Licensing: CC v3.0 Share-Alike You are welcome to use this library for commercial purposes.
op-amp: Copyright (C) 2008, Bob Starr
inductor-wurth: Copyright (C) 2010, Bob Starr
supply4: Copyright (C) 2007, Bob Starr
